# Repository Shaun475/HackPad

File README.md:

# Shaun's Epic HackPad

This sigma HackPad is a numpad style doo dad.

[Bill of Materials](./BOM.md)

[Devlog](./Devlog.md)

## Pictures

![case back view] ()

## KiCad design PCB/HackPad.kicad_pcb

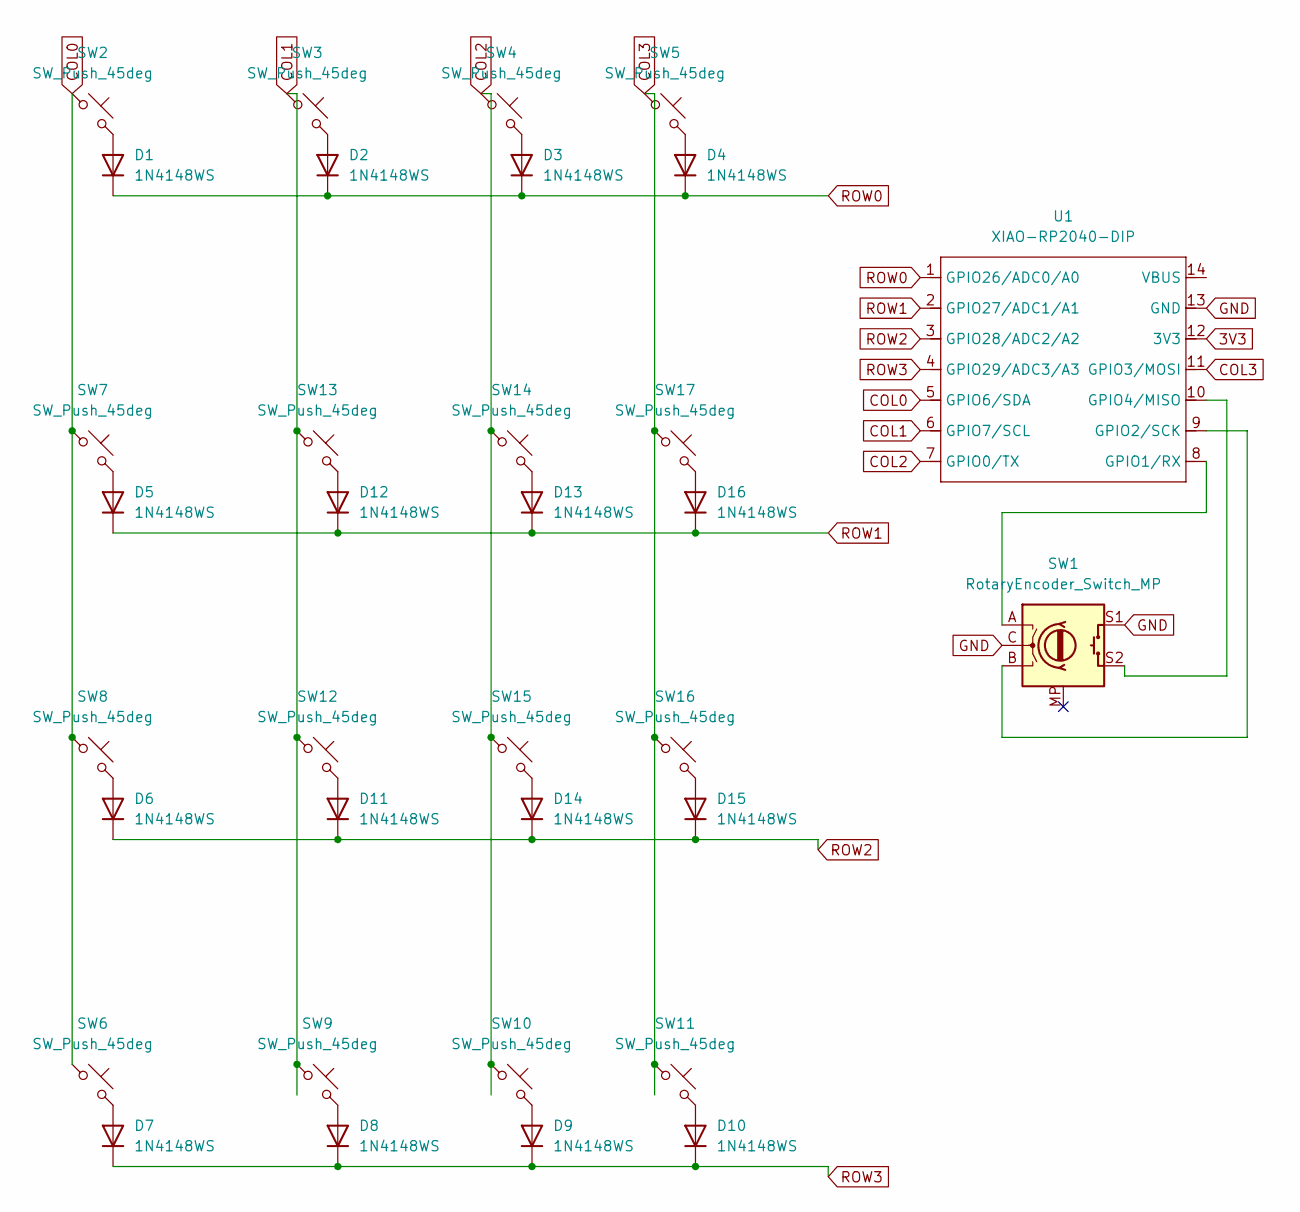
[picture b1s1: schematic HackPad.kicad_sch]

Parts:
D1, D2, D3, D4, D5, D6, D7, D8, D9, D10, D11, D12, D13, D14, D15, D16: 1N4148WS; D_SOD-323
SW1: RotaryEncoder_Switch_MP; RotaryEncoder_Alps_EC11E-Switch_Vertical_H20mm_MountingHoles
SW2, SW3, SW4, SW6, SW7, SW8, SW9, SW10, SW12, SW13, SW14, SW15, SW16: SW_Push_45deg; SW_Cherry_MX_1.00u_PCB
SW5, SW11, SW17: SW_Push_45deg; SW_Cherry_MX_2.00u_PCB
U1: XIAO-RP2040-DIP

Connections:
3V3: U1.12 (3V3)
COL0: SW2.1, SW6.1, SW7.1, SW8.1, U1.5 (GPIO6/SDA)
COL1: SW3.1, SW9.1, SW12.1, SW13.1, U1.6 (GPIO7/SCL)
COL2: SW4.1, SW10.1, SW14.1, SW15.1, U1.7 (GPIO0/TX)
COL3: SW5.1, SW11.1, SW16.1, SW17.1, U1.11 (GPIO3/MOSI)
GND: SW1.C, SW1.S1, U1.13 (GND)
unnamed: D1.2 (A), SW2.2
unnamed: D2.2 (A), SW3.2
unnamed: D3.2 (A), SW4.2
unnamed: D4.2 (A), SW5.2
unnamed: D5.2 (A), SW7.2
unnamed: D6.2 (A), SW8.2
unnamed: D7.2 (A), SW6.2
unnamed: D8.2 (A), SW9.2
unnamed: D9.2 (A), SW10.2
unnamed: D10.2 (A), SW11.2
unnamed: D11.2 (A), SW12.2
unnamed: D12.2 (A), SW13.2
unnamed: D13.2 (A), SW14.2
unnamed: D14.2 (A), SW15.2
unnamed: D15.2 (A), SW16.2
unnamed: D16.2 (A), SW17.2
unnamed: SW1.A, U1.8 (GPIO1/RX)
unnamed: SW1.B, U1.9 (GPIO2/SCK)
unnamed: SW1.S2, U1.10 (GPIO4/MISO)
ROW0: D1.1 (K), D2.1 (K), D3.1 (K), D4.1 (K), U1.1 (GPIO26/ADC0/A0)
ROW1: D5.1 (K), D12.1 (K), D13.1 (K), D16.1 (K), U1.2 (GPIO27/ADC1/A1)
ROW2: D6.1 (K), D11.1 (K), D14.1 (K), D15.1 (K), U1.3 (GPIO28/ADC2/A2)
ROW3: D7.1 (K), D8.1 (K), D9.1 (K), D10.1 (K), U1.4 (GPIO29/ADC3/A3)

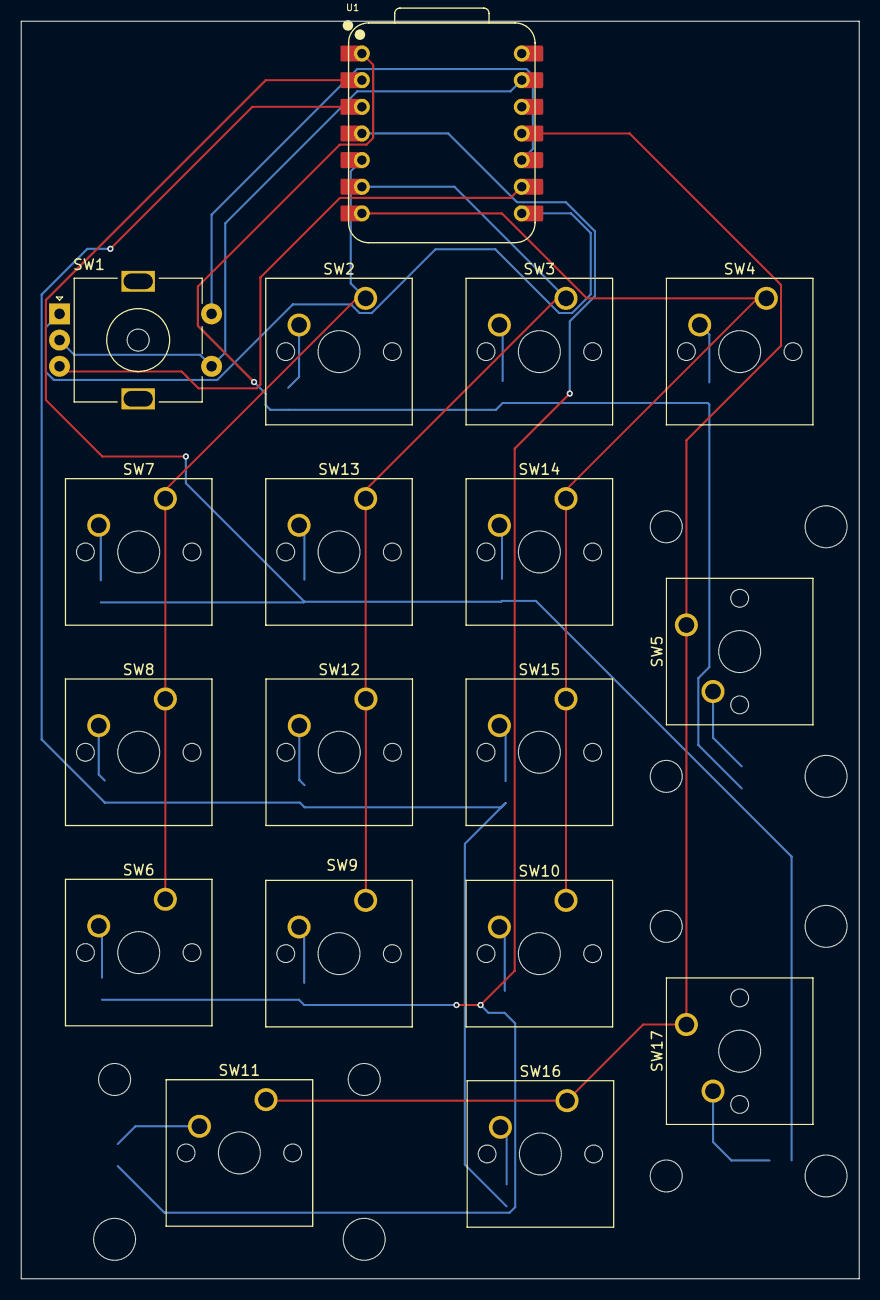
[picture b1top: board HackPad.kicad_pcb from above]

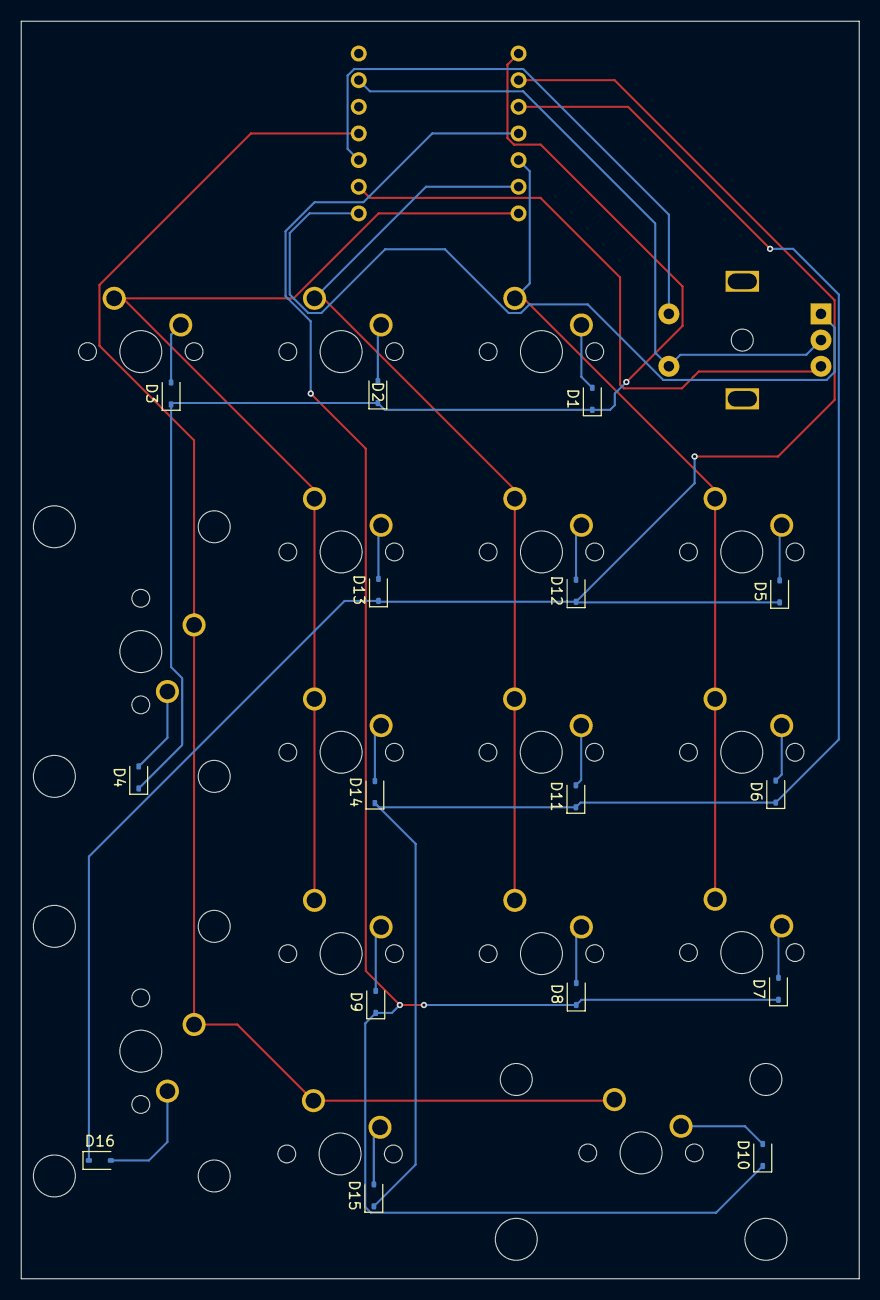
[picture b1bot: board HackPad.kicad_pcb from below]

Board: 2 copper layers, 79.9 x 119.9 mm, 34 parts (16 on the bottom side), 28 nets.

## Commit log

2025-06-30 finished system
2025-06-30 fixed filee structure
